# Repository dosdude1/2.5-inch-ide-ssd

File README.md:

# 2.5-inch IDE SSD

A custom-designed IDE SSD for use in any machine that utilizies a 2.5" IDE hard disk. 

The design is based on the Silicon Motion SM2236 controller, and is compatible with up to four 512Gbit (64GB) BGA152 or BGA132 NANDs.

## Important Info

WARNING: THE SILICON MOTION SM2236 CONTROLLER PINOUT AND IMPLEMENTATION HAVE BEEN REVERSE ENGINEERED FROM OPEN DOCUMENTS AND SALVAGED PCBS, ALL OF WHICH HAVE BEEN LEGALLY OBTAINED. DO NOT EXPECT THIS TO BE CORRECT, CHECK FOR YOURSELF.

### NAND Info

- The NAND ICs used on this PCB must be explicitly supported by the SM2236 controller. All supported NAND ICs are listed in the SM2236 MPTool, or "Mass Production Tool". Be sure to verify compatibility before installing NANDs.

- All installed NAND ICs must match.

- Check the datasheet for your desired NAND ICs to determine their rated I/O voltage, and populate the correct resistor position on the board to set either 3.3V or 1.8V. This is shown in the schematic diagram.

## Programming

Upon the completion of board assembly, the SM2236 controller must be programmed for the NAND ICs you have installed. To do so, you must utilize an IDE to USB adapter to connect the drive to a PC running Windows (using native IDE for this will not work). Then, the SM2236 MPTool must be used to set all the desired drive information, select the part number of NAND ICs you have installed, and program the drive.

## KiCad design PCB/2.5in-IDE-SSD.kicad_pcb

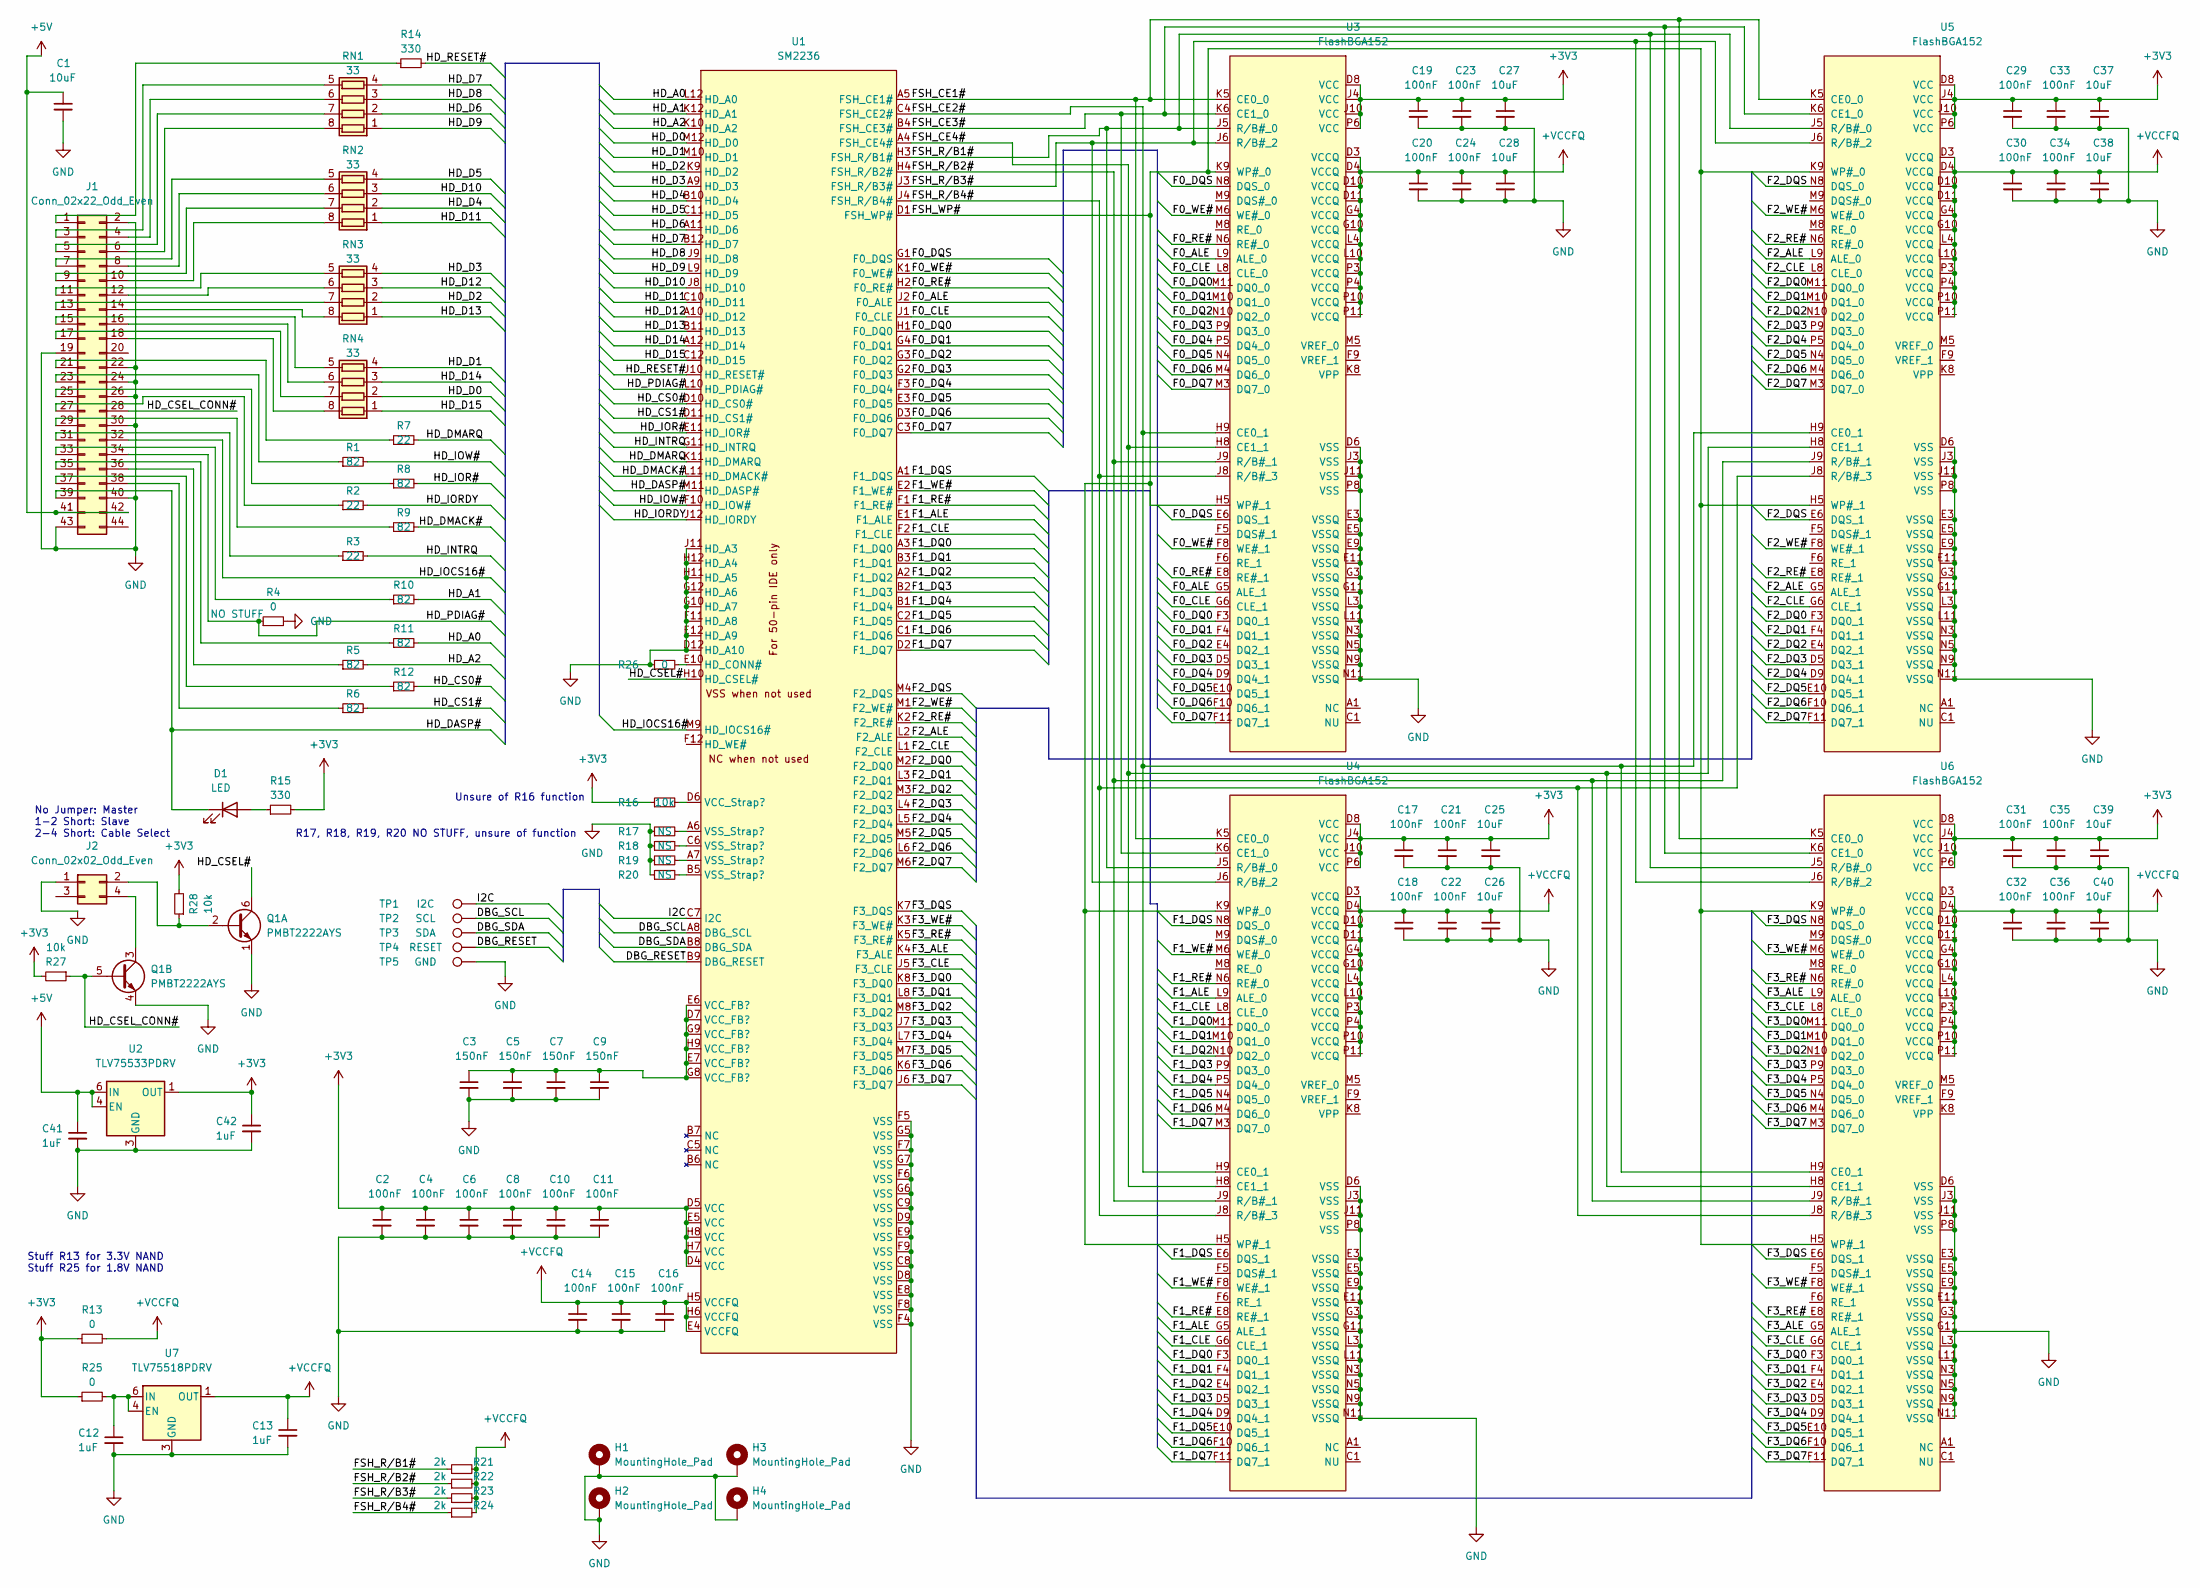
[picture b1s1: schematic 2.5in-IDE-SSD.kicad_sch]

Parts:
C1: 10uF; C_0805_2012Metric; LCSC C15850
C2, C4, C6, C8, C10, C11, C14, C15, C16, C17, C18, C19, C20, C21, C22, C23, C24, C29, C30, C31, C32, C33, C34, C35, C36: 100nF; C_0402_1005Metric; LCSC C1525
C3, C5, C7, C9: 150nF; C_0402_1005Metric; LCSC C576725
C12, C13, C41, C42: 1uF; C_0603_1608Metric; LCSC C5673
C25, C26, C27, C28, C37, C38, C39, C40: 10uF; C_0603_1608Metric; LCSC C1691
D1: LED; LED_0603_1608Metric; LCSC C5160703
H1, H2, H3, H4: MountingHole_Pad; MountingHole_2.2mm_M2_ISO7380_Pad_TopBottom
J1: Conn_02x22_Odd_Even; 2x22_2mm_border_conn
J2: Conn_02x02_Odd_Even; 2x2_2mm_border_conn
Q1: PMBT2222AYS; SOT-363_SC-70-6
R1, R5, R6, R8, R9, R10, R11, R12: 82; R_0402_1005Metric; LCSC C163453
R2, R3, R7: 22; R_0402_1005Metric; LCSC C114765
R4, R26: 0; R_0402_1005Metric; LCSC C60485
R13, R25: 0; R_0603_1608Metric; LCSC C100044
R14, R15: 330; R_0402_1005Metric; LCSC C105875
R16, R27, R28: 10k; R_0402_1005Metric; LCSC C60490
R17, R18, R19, R20: NS; R_0402_1005Metric
R21, R22, R23, R24: 2k; R_0402_1005Metric; LCSC C60488
RN1, RN2, RN3, RN4: 33; R_Array_Convex_4x0402; LCSC C136851
TP1: I2C; TestPoint_Pad_1.0x1.0mm
TP2: SCL; TestPoint_Pad_1.0x1.0mm
TP3: SDA; TestPoint_Pad_1.0x1.0mm
TP4: RESET; TestPoint_Pad_1.0x1.0mm
TP5: GND; TestPoint_Pad_1.0x1.0mm
U1: SM2236; BGA-144_12x12_9.0x9.0mm
U2: TLV75533PDRV; WSON-6-1EP_2x2mm_P0.65mm_EP1x1.6mm
U3, U4, U5, U6: FlashBGA152; BGA-152_14x18mm_Layout13x17_P0.5mm
U7: TLV75518PDRV; WSON-6-1EP_2x2mm_P0.65mm_EP1x1.6mm

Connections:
+3V3: C2.1, C4.1, C6.1, C8.1, C10.1, C11.1, C17.1, C19.1, C21.1, C23.1, C25.1, C27.1, C29.1, C31.1, C33.1, C35.1, C37.1, C39.1, C42.1, R13.1, R15.2, R16.1, R25.1, R27.2, R28.2, U1.D4 (VCC), U1.D5 (VCC), U1.E5 (VCC), U1.H7 (VCC), U1.H8 (VCC), U2.1 (OUT), U3.D8 (VCC), U3.J4 (VCC), U3.J10 (VCC), U3.P6 (VCC), U4.D8 (VCC), U4.J4 (VCC), U4.J10 (VCC), U4.P6 (VCC), U5.D8 (VCC), U5.J4 (VCC), U5.J10 (VCC), U5.P6 (VCC), U6.D8 (VCC), U6.J4 (VCC), U6.J10 (VCC), U6.P6 (VCC)
+5V: C1.1, C41.1, J1.41, J1.42, U2.4 (EN), U2.6 (IN)
+VCCFQ: C13.1, C14.1, C15.1, C16.1, C18.1, C20.1, C22.1, C24.1, C26.1, C28.1, C30.1, C32.1, C34.1, C36.1, C38.1, C40.1, R13.2, R21.2, R22.2, R23.2, R24.2, U1.E4 (VCCFQ), U1.H5 (VCCFQ), U1.H6 (VCCFQ), U3.D3 (VCCQ), U3.D4 (VCCQ), U3.D10 (VCCQ), U3.D11 (VCCQ), U3.G4 (VCCQ), U3.G10 (VCCQ), U3.L4 (VCCQ), U3.L10 (VCCQ), U3.P3 (VCCQ), U3.P4 (VCCQ), U3.P10 (VCCQ), U3.P11 (VCCQ), U4.D3 (VCCQ), U4.D4 (VCCQ), U4.D10 (VCCQ), U4.D11 (VCCQ), U4.G4 (VCCQ), U4.G10 (VCCQ), U4.L4 (VCCQ), U4.L10 (VCCQ), U4.P3 (VCCQ), U4.P4 (VCCQ), U4.P10 (VCCQ), U4.P11 (VCCQ), U5.D3 (VCCQ), U5.D4 (VCCQ), U5.D10 (VCCQ), U5.D11 (VCCQ), U5.G4 (VCCQ), U5.G10 (VCCQ), U5.L4 (VCCQ), U5.L10 (VCCQ), U5.P3 (VCCQ), U5.P4 (VCCQ), U5.P10 (VCCQ), U5.P11 (VCCQ), U6.D3 (VCCQ), U6.D4 (VCCQ), U6.D10 (VCCQ), U6.D11 (VCCQ), U6.G4 (VCCQ), U6.G10 (VCCQ), U6.L4 (VCCQ), U6.L10 (VCCQ), U6.P3 (VCCQ), U6.P4 (VCCQ), U6.P10 (VCCQ), U6.P11 (VCCQ), U7.1 (OUT)
/DBG_RESET: TP4.1, U1.B9 (DBG_RESET); also elsewhere on the board
/DBG_SCL: TP2.1, U1.A8 (DBG_SCL); also elsewhere on the board
/DBG_SDA: TP3.1, U1.B8 (DBG_SDA); also elsewhere on the board
/F0_ALE: U1.J2 (F0_ALE), U3.G5 (ALE_1), U3.L9 (ALE_0)
/F0_CLE: U1.J1 (F0_CLE), U3.G6 (CLE_1), U3.L8 (CLE_0)
/F0_DQ0: U1.H1 (F0_DQ0), U3.F3 (DQ0_1), U3.M11 (DQ0_0)
/F0_DQ1: U1.G4 (F0_DQ1), U3.F4 (DQ1_1), U3.M10 (DQ1_0)
/F0_DQ2: U1.G3 (F0_DQ2), U3.E4 (DQ2_1), U3.N10 (DQ2_0)
/F0_DQ3: U1.G2 (F0_DQ3), U3.D5 (DQ3_1), U3.P9 (DQ3_0)
/F0_DQ4: U1.F3 (F0_DQ4), U3.D9 (DQ4_1), U3.P5 (DQ4_0)
/F0_DQ5: U1.E3 (F0_DQ5), U3.E10 (DQ5_1), U3.N4 (DQ5_0)
/F0_DQ6: U1.D3 (F0_DQ6), U3.F10 (DQ6_1), U3.M4 (DQ6_0)
/F0_DQ7: U1.C3 (F0_DQ7), U3.F11 (DQ7_1), U3.M3 (DQ7_0)
/F0_DQS: U1.G1 (F0_DQS), U3.E6 (DQS_1), U3.N8 (DQS_0)
/F0_RE#: U1.H2 (F0_RE#), U3.E8 (RE#_1), U3.N6 (RE#_0)
/F0_WE#: U1.K1 (F0_WE#), U3.F8 (WE#_1), U3.M6 (WE#_0)
/F1_ALE: U1.E1 (F1_ALE), U4.G5 (ALE_1), U4.L9 (ALE_0)
/F1_CLE: U1.F2 (F1_CLE), U4.G6 (CLE_1), U4.L8 (CLE_0)
/F1_DQ0: U1.A3 (F1_DQ0), U4.F3 (DQ0_1), U4.M11 (DQ0_0)
/F1_DQ1: U1.B3 (F1_DQ1), U4.F4 (DQ1_1), U4.M10 (DQ1_0)
/F1_DQ2: U1.A2 (F1_DQ2), U4.E4 (DQ2_1), U4.N10 (DQ2_0)
/F1_DQ3: U1.B2 (F1_DQ3), U4.D5 (DQ3_1), U4.P9 (DQ3_0)
/F1_DQ4: U1.B1 (F1_DQ4), U4.D9 (DQ4_1), U4.P5 (DQ4_0)
/F1_DQ5: U1.C2 (F1_DQ5), U4.E10 (DQ5_1), U4.N4 (DQ5_0)
/F1_DQ6: U1.C1 (F1_DQ6), U4.F10 (DQ6_1), U4.M4 (DQ6_0)
/F1_DQ7: U1.D2 (F1_DQ7), U4.F11 (DQ7_1), U4.M3 (DQ7_0)
/F1_DQS: U1.A1 (F1_DQS), U4.E6 (DQS_1), U4.N8 (DQS_0)
/F1_RE#: U1.F1 (F1_RE#), U4.E8 (RE#_1), U4.N6 (RE#_0)
/F1_WE#: U1.E2 (F1_WE#), U4.F8 (WE#_1), U4.M6 (WE#_0)
/F2_ALE: U1.L2 (F2_ALE), U5.G5 (ALE_1), U5.L9 (ALE_0)
/F2_CLE: U1.L1 (F2_CLE), U5.G6 (CLE_1), U5.L8 (CLE_0)
/F2_DQ0: U1.M2 (F2_DQ0), U5.F3 (DQ0_1), U5.M11 (DQ0_0)
/F2_DQ1: U1.L3 (F2_DQ1), U5.F4 (DQ1_1), U5.M10 (DQ1_0)
/F2_DQ2: U1.M3 (F2_DQ2), U5.E4 (DQ2_1), U5.N10 (DQ2_0)
/F2_DQ3: U1.L4 (F2_DQ3), U5.D5 (DQ3_1), U5.P9 (DQ3_0)
/F2_DQ4: U1.L5 (F2_DQ4), U5.D9 (DQ4_1), U5.P5 (DQ4_0)
/F2_DQ5: U1.M5 (F2_DQ5), U5.E10 (DQ5_1), U5.N4 (DQ5_0)
/F2_DQ6: U1.L6 (F2_DQ6), U5.F10 (DQ6_1), U5.M4 (DQ6_0)
/F2_DQ7: U1.M6 (F2_DQ7), U5.F11 (DQ7_1), U5.M3 (DQ7_0)
/F2_DQS: U1.M4 (F2_DQS), U5.E6 (DQS_1), U5.N8 (DQS_0)
/F2_RE#: U1.K2 (F2_RE#), U5.E8 (RE#_1), U5.N6 (RE#_0)
/F2_WE#: U1.M1 (F2_WE#), U5.F8 (WE#_1), U5.M6 (WE#_0)
/F3_ALE: U1.K4 (F3_ALE), U6.G5 (ALE_1), U6.L9 (ALE_0)
/F3_CLE: U1.J5 (F3_CLE), U6.G6 (CLE_1), U6.L8 (CLE_0)
/F3_DQ0: U1.K8 (F3_DQ0), U6.F3 (DQ0_1), U6.M11 (DQ0_0)
/F3_DQ1: U1.L8 (F3_DQ1), U6.F4 (DQ1_1), U6.M10 (DQ1_0)
/F3_DQ2: U1.M8 (F3_DQ2), U6.E4 (DQ2_1), U6.N10 (DQ2_0)
/F3_DQ3: U1.J7 (F3_DQ3), U6.D5 (DQ3_1), U6.P9 (DQ3_0)
/F3_DQ4: U1.L7 (F3_DQ4), U6.D9 (DQ4_1), U6.P5 (DQ4_0)
/F3_DQ5: U1.M7 (F3_DQ5), U6.E10 (DQ5_1), U6.N4 (DQ5_0)
/F3_DQ6: U1.K6 (F3_DQ6), U6.F10 (DQ6_1), U6.M4 (DQ6_0)
/F3_DQ7: U1.J6 (F3_DQ7), U6.F11 (DQ7_1), U6.M3 (DQ7_0)
/F3_DQS: U1.K7 (F3_DQS), U6.E6 (DQS_1), U6.N8 (DQS_0)
/F3_RE#: U1.K5 (F3_RE#), U6.E8 (RE#_1), U6.N6 (RE#_0)
/F3_WE#: U1.K3 (F3_WE#), U6.F8 (WE#_1), U6.M6 (WE#_0)
/FSH_CE1#: U1.A5 (FSH_CE1#), U3.K5 (CE0_0), U4.K5 (CE0_0), U5.K5 (CE0_0), U6.K5 (CE0_0)
/FSH_CE2#: U1.C4 (FSH_CE2#), U3.H9 (CE0_1), U4.H9 (CE0_1), U5.H9 (CE0_1), U6.H9 (CE0_1)
/FSH_CE3#: U1.B4 (FSH_CE3#), U3.K6 (CE1_0), U4.K6 (CE1_0), U5.K6 (CE1_0), U6.K6 (CE1_0)
/FSH_CE4#: U1.A4 (FSH_CE4#), U3.H8 (CE1_1), U4.H8 (CE1_1), U5.H8 (CE1_1), U6.H8 (CE1_1)
/FSH_R/B1#: R21.1, U1.H3 (FSH_R/B1#), U3.J5 (R/B#_0), U4.J5 (R/B#_0), U5.J5 (R/B#_0), U6.J5 (R/B#_0)
/FSH_R/B2#: R22.1, U1.H4 (FSH_R/B2#), U3.J9 (R/B#_1), U4.J9 (R/B#_1), U5.J9 (R/B#_1), U6.J9 (R/B#_1)
/FSH_R/B3#: R23.1, U1.J3 (FSH_R/B3#), U3.J6 (R/B#_2), U4.J6 (R/B#_2), U5.J6 (R/B#_2), U6.J6 (R/B#_2)
/FSH_R/B4#: R24.1, U1.J4 (FSH_R/B4#), U3.J8 (R/B#_3), U4.J8 (R/B#_3), U5.J8 (R/B#_3), U6.J8 (R/B#_3)
/FSH_WP#: U1.D1 (FSH_WP#), U3.H5 (WP#_1), U3.K9 (WP#_0), U4.H5 (WP#_1), U4.K9 (WP#_0), U5.H5 (WP#_1), U5.K9 (WP#_0), U6.H5 (WP#_1), U6.K9 (WP#_0)
/HD_A0: R11.2, U1.L12 (HD_A0)
/HD_A1: R10.2, U1.K12 (HD_A1)
/HD_A2: R5.2, U1.K10 (HD_A2)
/HD_CS0#: R12.2, U1.D10 (HD_CS0#)
/HD_CS1#: R6.2, U1.D11 (HD_CS1#)
/HD_CSEL#: Q1.6 (C1), U1.H10 (HD_CSEL#)
/HD_CSEL_CONN#: J1.28, Q1.5 (B2), R27.1
/HD_D0: RN4.2 (R2.1), U1.M12 (HD_D0)
/HD_D1: RN4.4 (R4.1), U1.M10 (HD_D1)
/HD_D2: RN3.2 (R2.1), U1.K9 (HD_D2)
/HD_D3: RN3.4 (R4.1), U1.A9 (HD_D3)
/HD_D4: RN2.2 (R2.1), U1.B10 (HD_D4)
/HD_D5: RN2.4 (R4.1), U1.C11 (HD_D5)
/HD_D6: RN1.2 (R2.1), U1.A11 (HD_D6)
/HD_D7: RN1.4 (R4.1), U1.B12 (HD_D7)
/HD_D8: RN1.3 (R3.1), U1.J9 (HD_D8)
/HD_D9: RN1.1 (R1.1), U1.L9 (HD_D9)
/HD_D10: RN2.3 (R3.1), U1.J8 (HD_D10)
/HD_D11: RN2.1 (R1.1), U1.C10 (HD_D11)
/HD_D12: RN3.3 (R3.1), U1.A10 (HD_D12)
/HD_D13: RN3.1 (R1.1), U1.B11 (HD_D13)
/HD_D14: RN4.3 (R3.1), U1.A12 (HD_D14)
/HD_D15: RN4.1 (R1.1), U1.C12 (HD_D15)
/HD_DASP#: D1.1 (K), J1.39, U1.M11 (HD_DASP#)
/HD_DMACK#: R9.2, U1.L11 (HD_DMACK#)
/HD_DMARQ: R7.2, U1.K11 (HD_DMARQ)
/HD_INTRQ: R3.2, U1.G11 (HD_INTRQ)
/HD_IOCS16#: J1.32, U1.M9 (HD_IOCS16#)
/HD_IOR#: R8.2, U1.E11 (HD_IOR#)
/HD_IORDY: R2.2, U1.J12 (HD_IORDY)
/HD_IOW#: R1.2, U1.F10 (HD_IOW#)
/HD_PDIAG#: J1.34, R4.1, U1.L10 (HD_PDIAG#)
/HD_RESET#: R14.2, U1.J10 (HD_RESET#)
/I2C: TP1.1, U1.C7 (I2C); also elsewhere on the board
GND: C1.2, C2.2, C3.2, C4.2, C5.2, C6.2, C7.2, C8.2, C9.2, C10.2, C11.2, C12.2, C13.2, C14.2, C15.2, C16.2, C17.2, C18.2, C19.2, C20.2, C21.2, C22.2, C23.2, C24.2, C25.2, C26.2, C27.2, C28.2, C29.2, C30.2, C31.2, C32.2, C33.2, C34.2, C35.2, C36.2, C37.2, C38.2, C39.2, C40.2, C41.2, C42.2, H1.1, H2.1, H3.1, H4.1, J1.2, J1.19, J1.22, J1.24, J1.26, J1.30, J1.40, J1.43, J2.1, Q1.1 (E1), Q1.4 (E2), R4.2, R17.1, R18.1, R19.1, R20.1, R26.1, TP5.1, U1.C8 (VSS), U1.C9 (VSS), U1.D8 (VSS), U1.D9 (VSS), U1.D12 (HD_A10), U1.E8 (VSS), U1.E9 (VSS), U1.E12 (HD_A9), U1.F4 (VSS), U1.F5 (VSS), U1.F6 (VSS), U1.F7 (VSS), U1.F8 (VSS), U1.F9 (VSS), U1.F11 (HD_A8), U1.G5 (VSS), U1.G6 (VSS), U1.G7 (VSS), U1.G10 (HD_A7), U1.G12 (HD_A6), U1.H11 (HD_A5), U1.H12 (HD_A4), U1.J11 (HD_A3), U2.3 (GND), U2.7 (GND), U3.D6 (VSS), U3.E3 (VSSQ), U3.E5 (VSSQ), U3.E9 (VSSQ), U3.E11 (VSSQ), U3.G3 (VSSQ), U3.G11 (VSSQ), U3.J3 (VSS), U3.J11 (VSS), U3.L3 (VSSQ), U3.L11 (VSSQ), U3.N3 (VSSQ), U3.N5 (VSSQ), U3.N9 (VSSQ), U3.N11 (VSSQ), U3.P8 (VSS), U4.D6 (VSS), U4.E3 (VSSQ), U4.E5 (VSSQ), U4.E9 (VSSQ), U4.E11 (VSSQ), U4.G3 (VSSQ), U4.G11 (VSSQ), U4.J3 (VSS), U4.J11 (VSS), U4.L3 (VSSQ), U4.L11 (VSSQ), U4.N3 (VSSQ), U4.N5 (VSSQ), U4.N9 (VSSQ), U4.N11 (VSSQ), U4.P8 (VSS), U5.D6 (VSS), U5.E3 (VSSQ), U5.E5 (VSSQ), U5.E9 (VSSQ), U5.E11 (VSSQ), U5.G3 (VSSQ), U5.G11 (VSSQ), U5.J3 (VSS), U5.J11 (VSS), U5.L3 (VSSQ), U5.L11 (VSSQ), U5.N3 (VSSQ), U5.N5 (VSSQ), U5.N9 (VSSQ), U5.N11 (VSSQ), U5.P8 (VSS), U6.D6 (VSS), U6.E3 (VSSQ), U6.E5 (VSSQ), U6.E9 (VSSQ), U6.E11 (VSSQ), U6.G3 (VSSQ), U6.G11 (VSSQ), U6.J3 (VSS), U6.J11 (VSS), U6.L3 (VSSQ), U6.L11 (VSSQ), U6.N3 (VSSQ), U6.N5 (VSSQ), U6.N9 (VSSQ), U6.N11 (VSSQ), U6.P8 (VSS), U7.3 (GND), U7.7 (GND); also elsewhere on the board
unnamed: C3.1, C5.1, C7.1, C9.1, U1.D7 (VCC_FB?), U1.E6 (VCC_FB?), U1.E7 (VCC_FB?), U1.G8 (VCC_FB?), U1.G9 (VCC_FB?), U1.H9 (VCC_FB?)
unnamed: C12.1, R25.2, U7.4 (EN), U7.6 (IN)
unnamed: D1.2 (A), R15.1
unnamed: J1.1, R14.1
unnamed: J1.3, RN1.5 (R4.2)
unnamed: J1.4, RN1.6 (R3.2)
unnamed: J1.5, RN1.7 (R2.2)
unnamed: J1.6, RN1.8 (R1.2)
unnamed: J1.7, RN2.5 (R4.2)
unnamed: J1.8, RN2.6 (R3.2)
unnamed: J1.9, RN2.7 (R2.2)
unnamed: J1.10, RN2.8 (R1.2)
unnamed: J1.11, RN3.5 (R4.2)
unnamed: J1.12, RN3.6 (R3.2)
unnamed: J1.13, RN3.7 (R2.2)
unnamed: J1.14, RN3.8 (R1.2)
unnamed: J1.15, RN4.5 (R4.2)
unnamed: J1.16, RN4.6 (R3.2)
unnamed: J1.17, RN4.7 (R2.2)
unnamed: J1.18, RN4.8 (R1.2)
unnamed: J1.21, R7.1
unnamed: J1.23, R1.1
unnamed: J1.25, R8.1
unnamed: J1.27, R2.1
unnamed: J1.29, R9.1
unnamed: J1.31, R3.1
unnamed: J1.33, R10.1
unnamed: J1.35, R11.1
unnamed: J1.36, R5.1
unnamed: J1.37, R12.1
unnamed: J1.38, R6.1
unnamed: J2.2, Q1.2 (B1), R28.1
unnamed: J2.4, Q1.3 (C2)
unnamed: R16.2, U1.D6 (VCC_Strap?)
unnamed: R17.2, U1.A6 (VSS_Strap?)
unnamed: R18.2, U1.C6 (VSS_Strap?)
unnamed: R19.2, U1.A7 (VSS_Strap?)
unnamed: R20.2, U1.B5 (VSS_Strap?)
unnamed: R26.2, U1.E10 (HD_CONN#)

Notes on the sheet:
No Jumper: Master 1-2 Short: Slave 2-4 Short: Cable Select
Stuff R13 for 3.3V NAND Stuff R25 for 1.8V NAND
Unsure of R16 function
R17, R18, R19, R20 NO STUFF, unsure of function

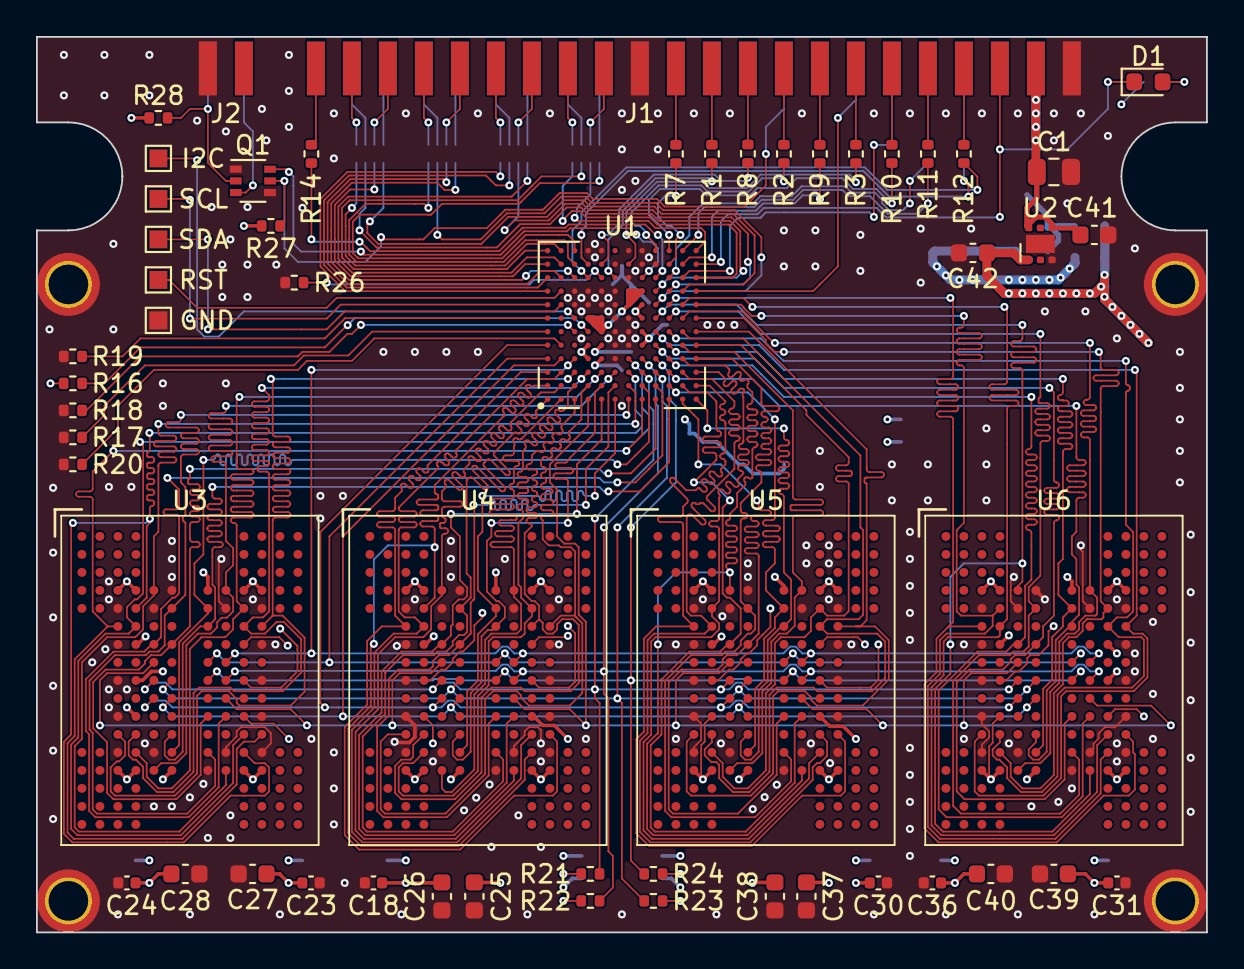
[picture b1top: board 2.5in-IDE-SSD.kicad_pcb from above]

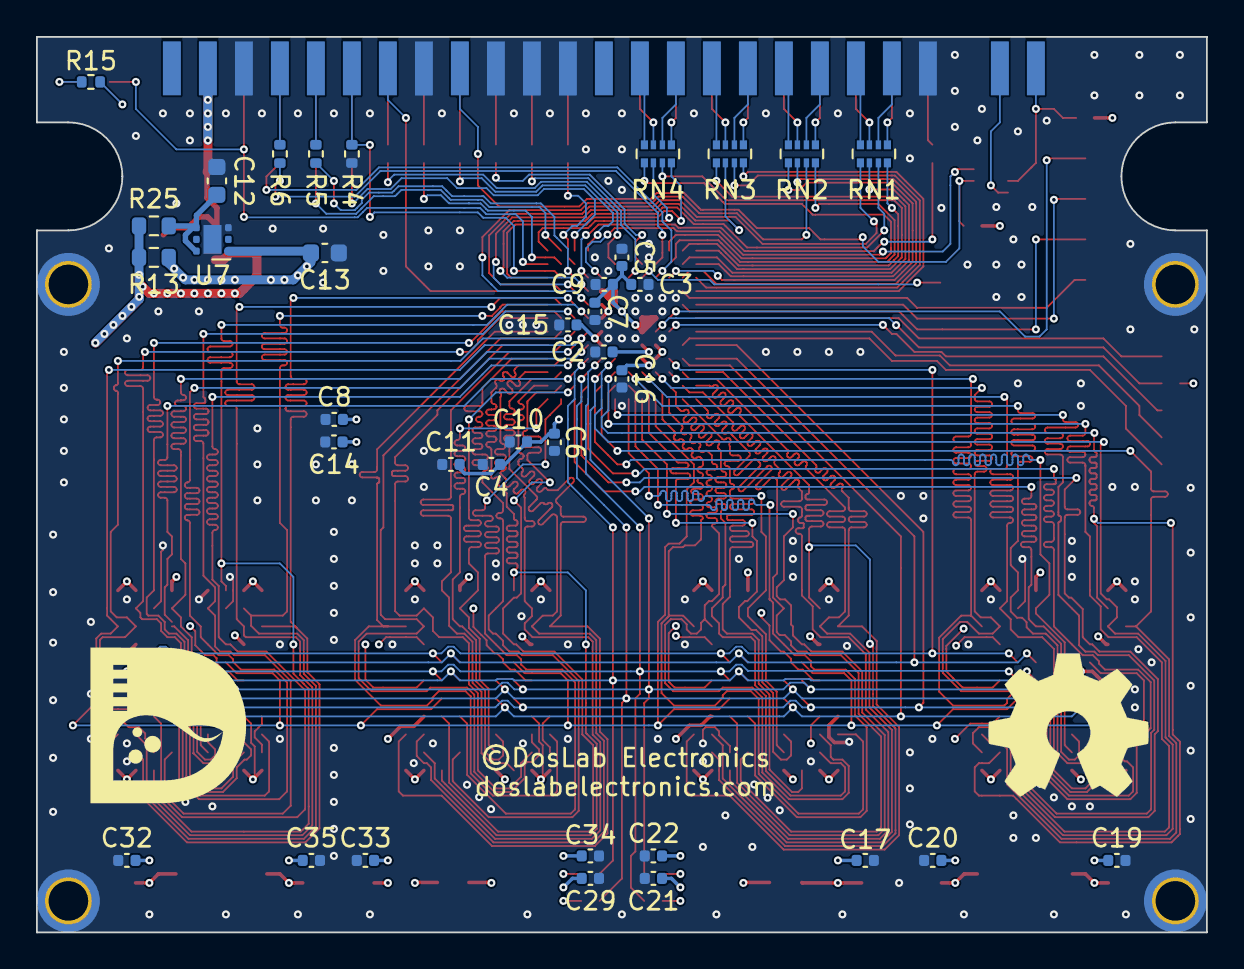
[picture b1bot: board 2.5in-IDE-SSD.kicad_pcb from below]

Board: 4 copper layers, 65.0 x 49.8 mm, 94 parts (36 on the bottom side), 141 nets.

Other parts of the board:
GND: GND; TestPoint_Pad_1.0x1.0mm
I2C: I2C; TestPoint_Pad_1.0x1.0mm
RST: RESET; TestPoint_Pad_1.0x1.0mm
SCL: SCL; TestPoint_Pad_1.0x1.0mm
SDA: SDA; TestPoint_Pad_1.0x1.0mm

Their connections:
/DBG_RESET: RST.1; also elsewhere on the board
/DBG_SCL: SCL.1; also elsewhere on the board
/DBG_SDA: SDA.1; also elsewhere on the board
/I2C: I2C.1; also elsewhere on the board
GND: GND.1; also elsewhere on the board

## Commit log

2023-01-18 Added gitignore
2023-01-18 Added PCB
2023-01-18 Added readme
2023-05-17 Reversed state of master/slave select, making master mode enabled when jumper is removed

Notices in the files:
PCB/2.5in-IDE-SSD.kicad_pcb:
©DosLab Electronics
